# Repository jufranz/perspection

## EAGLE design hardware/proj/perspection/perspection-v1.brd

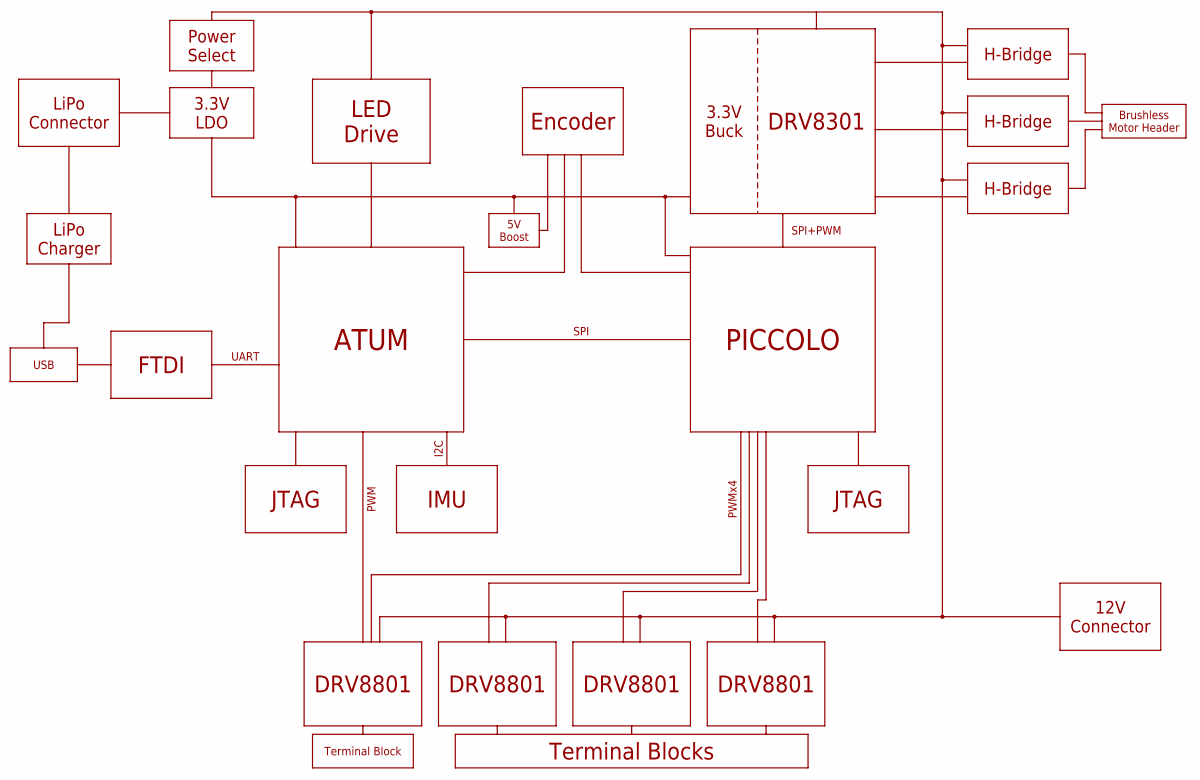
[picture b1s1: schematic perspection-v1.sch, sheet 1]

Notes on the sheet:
ATUM
PICCOLO
FTDI
SPI
UART
JTAG
DRV8301
H-Bridge
Brushless Motor Header
DRV8801
IMU
I2C
LED Drive
Terminal Blocks
Terminal Block
USB
Encoder
LiPo Charger
LiPo Connector
3.3V LDO
5V Boost
3.3V Buck
12V Connector
PWMx4
PWM
SPI+PWM
Power Select

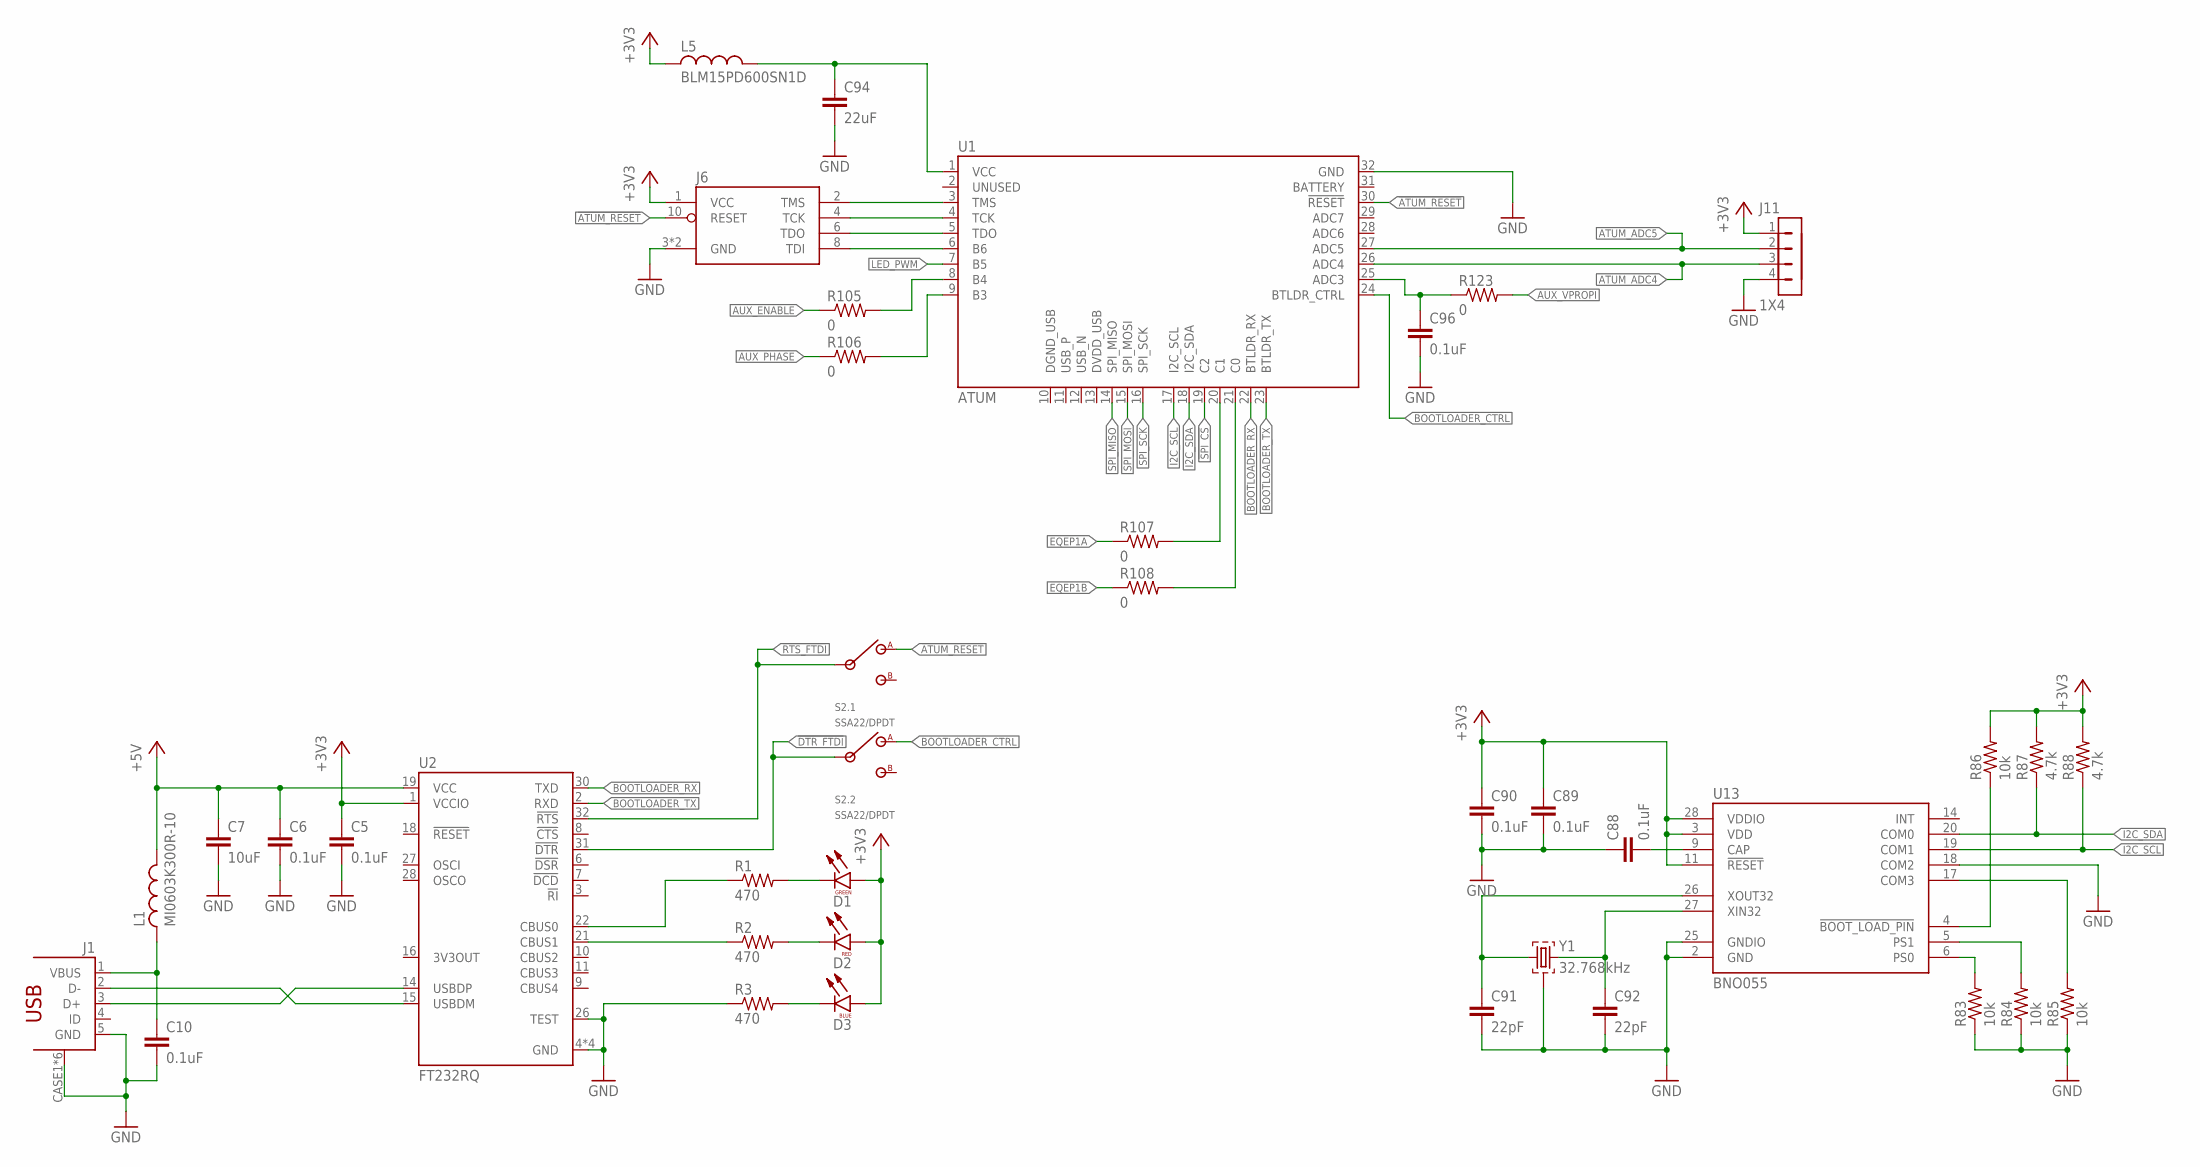
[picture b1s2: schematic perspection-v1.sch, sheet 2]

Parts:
C5, C6, C10, C88, C89, C90, C96: 0.1uF; C0402
C7: 10uF; C1206
C91, C92: 22pF; C0402
C94: 22uF; C1206
D1, D2, D3: LED0603
J1: MICRO-USB-10118192-0001LF; MICRO-USB
J6: JTAG-ARM_TC-10; TC2050-IDC
J11: 1X4; 1X4_0.1IN_THRUHOLE
L1: MI0603K300R-10; L0603; MFG_PN MI0603K300R-10
L5: BLM15PD600SN1D; L0402; MFG_PN BLM15PD600SN1D
R1, R2, R3: 470; R0402
R83, R84, R85, R86: 10k; R0402
R87, R88: 4.7k; R0402
R105, R106, R107, R108, R123: 0; R0402
S2: SSA22/DPDT
U1: ATUM
U2: FT232RQ; QFN32
U13: BNO055; LGA-28
Y1: 32.768kHz; SOJ-4

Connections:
!ATUM_RESET: J6.10 (RESET), S2.A1 (1), U1.30 (!RESET)
!DTR_FTDI: S2.COM2 (2), U2.31 (!DTR)
!RTS_FTDI: S2.COM1 (2), U2.32 (!RTS)
!SPI_CS: U1.19 (C2); also elsewhere on the board
+3V3: C5.1, C89.1, C90.1, D1.ANODE, D2.ANODE, D3.ANODE, J6.1 (VCC), J11.1, L5.1, R86.2, R87.2, R88.2, U2.1 (VCCIO), U13.3 (VDD), U13.11 (!RESET), U13.28 (VDDIO); also elsewhere on the board
+5V: C6.1, C7.1, L1.2, U2.19 (VCC); also elsewhere on the board
ATUM_ADC4: J11.3, U1.26 (ADC4)
ATUM_ADC5: J11.2, U1.27 (ADC5)
ATUM_C0: R108.2, U1.21 (C0)
ATUM_C1: R107.2, U1.20 (C1)
ATUM_TCK: J6.4 (TCK), U1.4 (TCK)
ATUM_TDO: J6.6 (TDO), U1.5 (TDO)
ATUM_TMS: J6.2 (TMS), U1.3 (TMS)
AUX_ENABLE: R105.1; also elsewhere on the board
AUX_PHASE: R106.1; also elsewhere on the board
AUX_VPROPI: R123.2; also elsewhere on the board
BOOTLOADER_CTRL: S2.A2 (1), U1.24 (BTLDR_CTRL)
BOOTLOADER_RX: U1.22 (BTLDR_RX), U2.30 (TXD)
BOOTLOADER_TX: U1.23 (BTLDR_TX), U2.2 (RXD)
D_N: J1.2 (D-), U2.15 (USBDM)
D_P: J1.3 (D+), U2.14 (USBDP)
EQEP1A: R107.1; also elsewhere on the board
EQEP1B: R108.1; also elsewhere on the board
GND: C5.2, C6.2, C7.2, C10.2, C88.1, C89.2, C90.2, C91.2, C92.2, C94.2, C96.2, J1.5 (GND), J1.CASE1 (MTN4), J1.CASE2 (MTN4), J1.CASE3 (MTN4), J1.CASE4 (MTN4), J1.CASE5 (MTN4), J1.CASE6 (MTN4), J6.3 (GND), J6.9 (GND), J11.4, R3.1, R83.1, R84.1, R85.1, U1.32 (GND), U2.4 (GND), U2.17 (GND), U2.20 (GND), U2.24 (GND), U2.26 (TEST), U13.2 (GND), U13.18 (COM2), U13.25 (GNDIO), Y1.2, Y1.3 (2); also elsewhere on the board
I2C_SCL: R88.1, U1.17 (I2C_SCL), U13.19 (COM1)
I2C_SDA: R87.1, U1.18 (I2C_SDA), U13.20 (COM0)
LED_PWM: U1.7 (B5); also elsewhere on the board
unnamed: D2.CATHODE, R2.2
unnamed: D1.CATHODE, R1.2
unnamed: R2.1, U2.21 (CBUS1)
unnamed: R1.1, U2.22 (CBUS0)
unnamed: D3.CATHODE, R3.2
unnamed: C96.1, R123.1, U1.25 (ADC3)
unnamed: C10.1, J1.1 (VBUS), L1.1
unnamed: R105.2, U1.8 (B4)
unnamed: R106.2, U1.9 (B3)
unnamed: R84.2, U13.5 (PS1)
unnamed: R83.2, U13.6 (PS0)
unnamed: C92.1, U13.27 (XIN32), Y1.4 (3)
unnamed: C88.2, U13.9 (CAP)
unnamed: C91.1, U13.26 (XOUT32), Y1.1
unnamed: R85.2, U13.17 (COM3)
unnamed: R86.1, U13.4 (!BOOT_LOAD_PIN)
unnamed: C94.1, L5.2, U1.1 (VCC)
unnamed: J6.8 (TDI), U1.6 (B6)
SPI_MISO: U1.14 (SPI_MISO); also elsewhere on the board
SPI_MOSI: U1.15 (SPI_MOSI); also elsewhere on the board
SPI_SCK: U1.16 (SPI_SCK); also elsewhere on the board

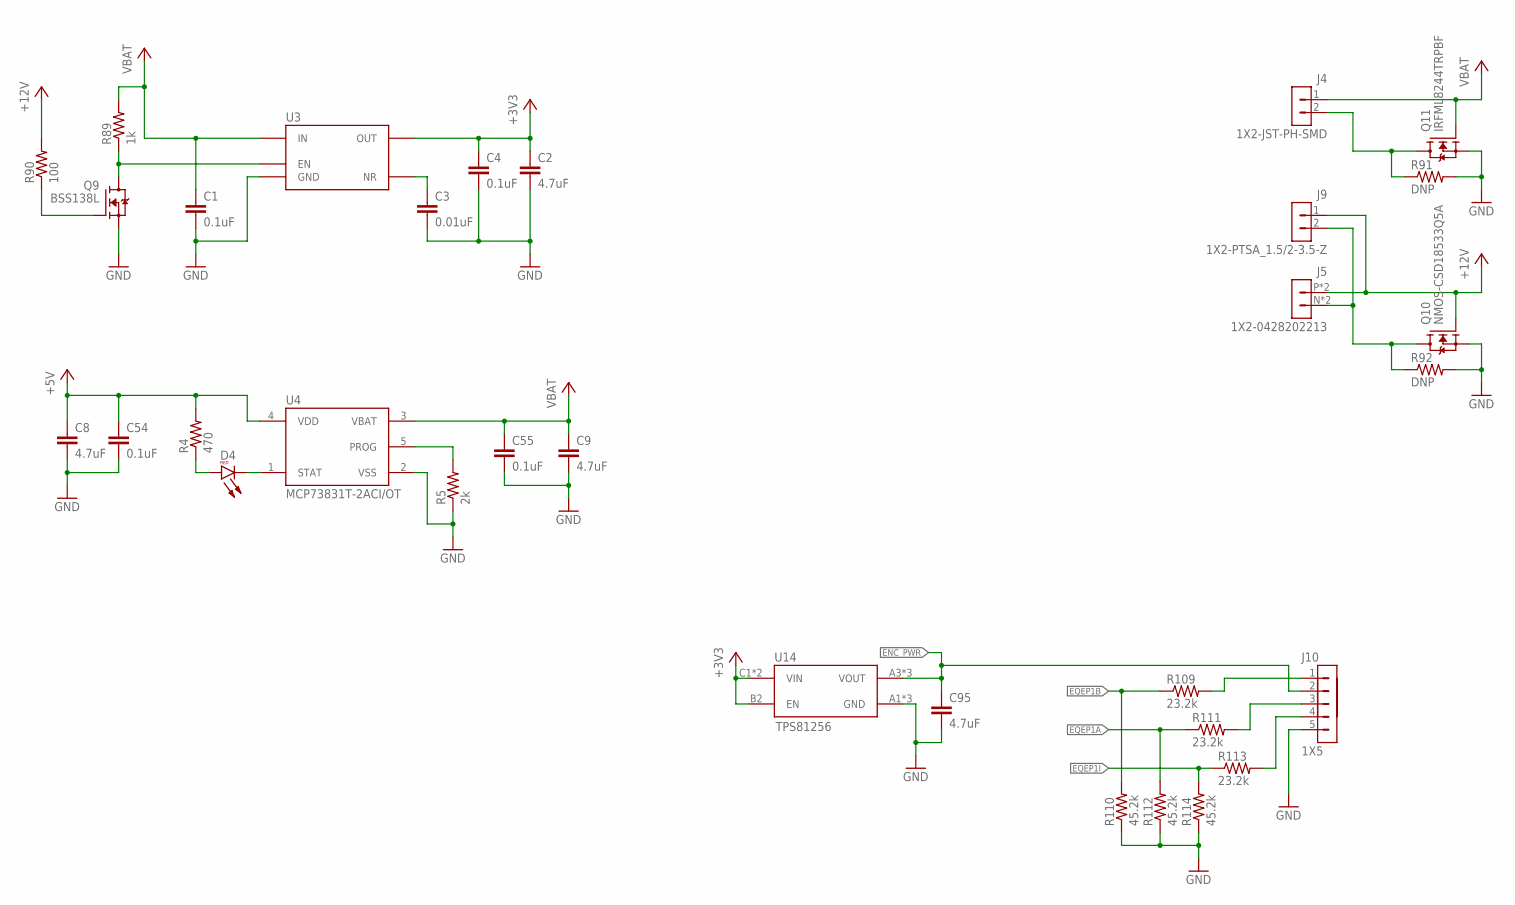
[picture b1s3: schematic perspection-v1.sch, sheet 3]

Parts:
C1, C4, C54, C55: 0.1uF; C0402
C2, C8, C9: 4.7uF; C0805
C3: 0.01uF; C0402
C95: 4.7uF; C0603
D4: LED0603
J4: 1X2-JST-PH-SMD; JST-PH-2-SMD
J5: 1X2-0428202213; MOLEX_SABRE_2POS
J9: 1X2-PTSA_1.5/2-3.5-Z; 3.5MM_PTSA_1.5/2-3.5-Z
J10: 1X5; 1X5_0.1IN_THRUHOLE
Q9: BSS138L; SOT23
Q10: NMOS-CSD18533Q5A; SON-5X6
Q11: IRFML8244TRPBF; SOT23
R4: 470; R0402
R5: 2k; R0402
R89: 1k; R0402
R90: 100; R0402
R91: DNP; R0402
R92: DNP; R0805
R109, R111, R113: 23.2k; R0402
R110, R112, R114: 45.2k; R0402
U3: TPS79933DDCR; SOT23-5
U4: MCP73831T-2ACI/OT; SOT23-5
U14: TPS81256; TI-SIP-9

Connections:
+3V3: C2.1, C4.1, U3.5 (OUT), U14.B2 (EN), U14.C1 (VIN), U14.C2 (VIN); also elsewhere on the board
+5V: C8.1, C54.1, R4.2, U4.4 (VDD); also elsewhere on the board
+12V: J5.P (1), J5.P2 (1), J9.1, Q10.G, R90.2; also elsewhere on the board
+12V_GND: J5.N (2), J5.N2 (2), J9.2, Q10.D, R92.1
ENC_PWR: C95.1, J10.2, U14.A3 (VOUT), U14.B3 (VOUT), U14.C3 (VOUT)
EQEP1A: R111.1, R112.2; also elsewhere on the board
EQEP1B: R109.1, R110.2; also elsewhere on the board
EQEP1I: R113.1, R114.2; also elsewhere on the board
GND: C1.2, C2.2, C3.2, C4.2, C8.2, C9.2, C54.2, C55.2, C95.2, J10.5, Q9.2 (S), Q10.S1 (S), Q10.S2 (S), Q10.S3 (S), Q11.2 (S), R5.1, R91.2, R92.2, R110.1, R112.1, R114.1, U3.2 (GND), U4.2 (VSS), U14.A1 (GND), U14.A2 (GND), U14.B1 (GND); also elsewhere on the board
unnamed: J10.1, R109.2
unnamed: D4.CATHODE, U4.1 (STAT)
unnamed: C3.1, U3.4 (NR)
unnamed: D4.ANODE, R4.1
unnamed: R5.2, U4.5 (PROG)
unnamed: J10.3, R111.2
unnamed: J10.4, R113.2
unnamed: Q9.3 (D), R89.1, U3.3 (EN)
unnamed: Q9.1 (G), R90.1
VBAT: C1.1, C9.1, C55.1, J4.1, Q11.1 (G), R89.2, U3.1 (IN), U4.3 (VBAT)
VBAT_GND: J4.2, Q11.3 (D), R91.1

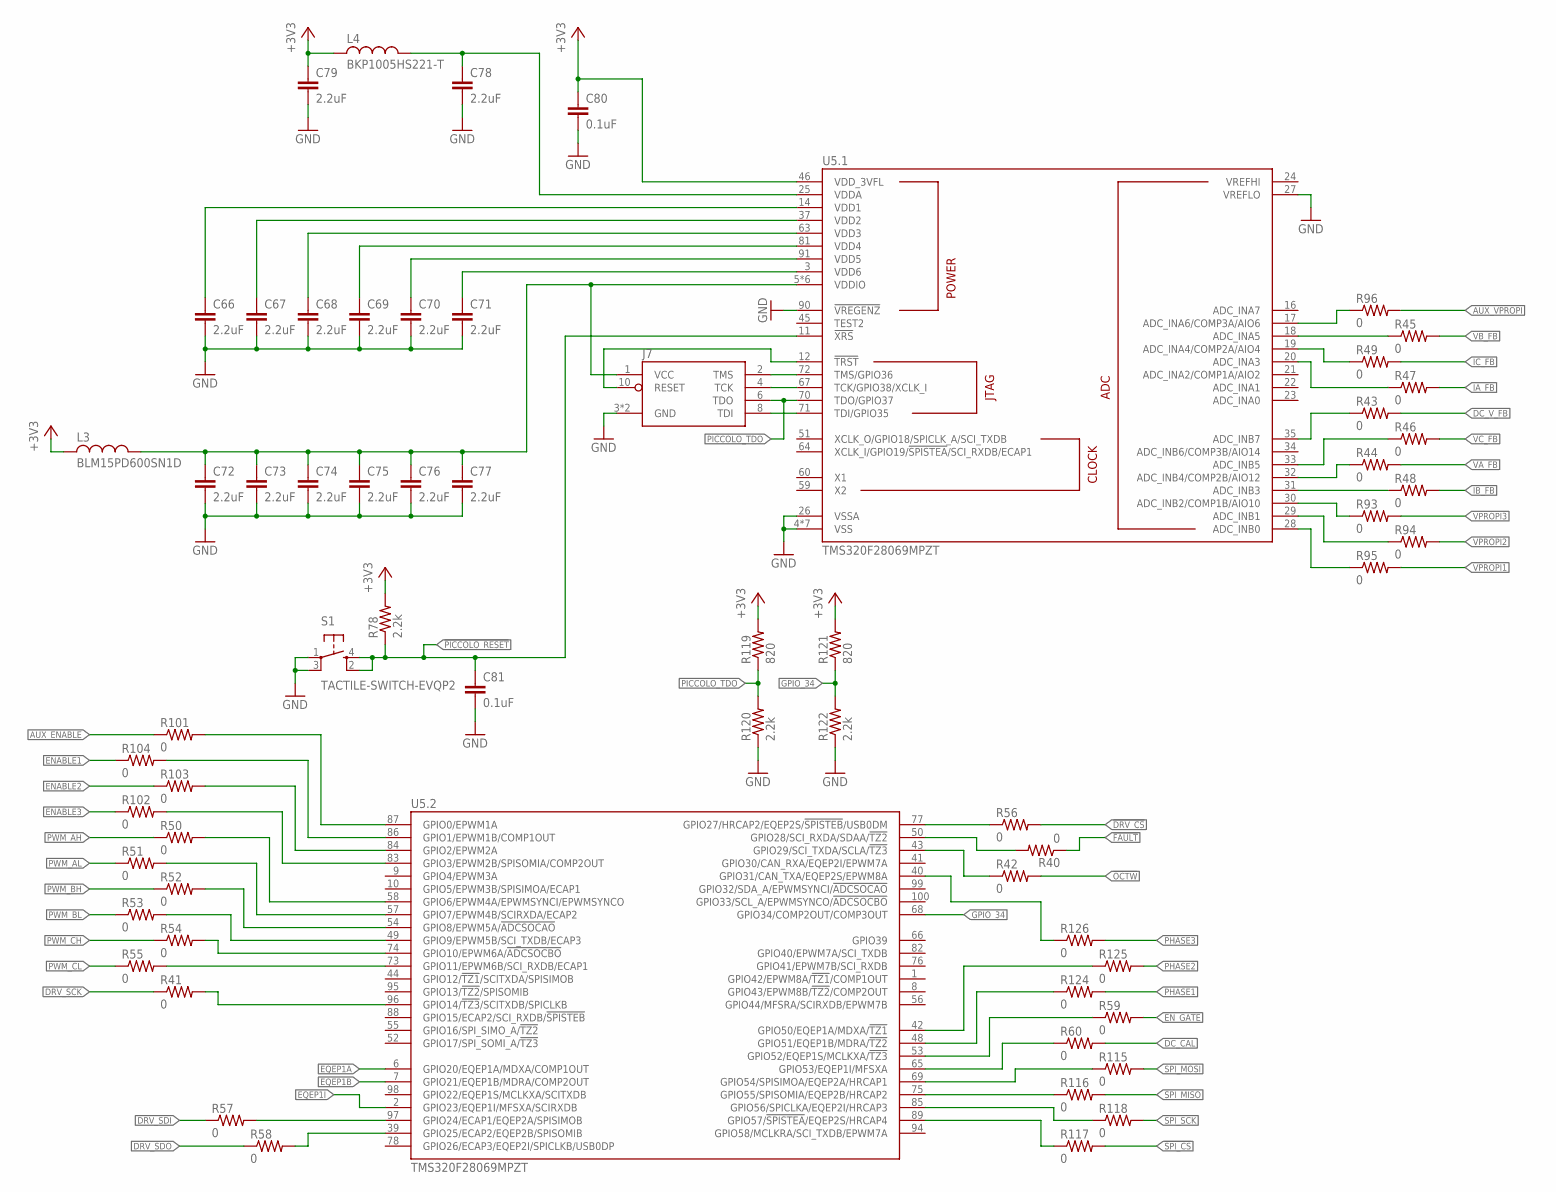
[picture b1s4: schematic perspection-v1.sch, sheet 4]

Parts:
C66, C67, C68, C69, C70, C71, C72, C73, C74, C75, C76, C77, C78, C79: 2.2uF; C0402
C80, C81: 0.1uF; C0402
J7: JTAG-ARM_TC-10; TC2050-IDC
L3: BLM15PD600SN1D; L0402; MFG_PN BLM15PD600SN1D
L4: BKP1005HS221-T; L0402
R40, R41, R42, R43, R44, R45, R46, R47, R48, R49, R50, R51, R52, R53, R54, R55, R56, R57, R58, R59, R60, R93, R94, R95, R96, R101, R102, R103, R104, R115, R116, R117, R118, R124, R125, R126: 0; R0402
R78, R120, R122: 2.2k; R0402
R119, R121: 820; R0402
S1: TACTILE-SWITCH-EVQP2; EVQP2
U5: TMS320F28069MPZT; TI-LQFP-100

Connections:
!DRV_CS: R56.2; also elsewhere on the board
!FAULT: R40.1; also elsewhere on the board
!OCTW: R42.2; also elsewhere on the board
!PICCOLO_RESET: C81.1, R78.1, S1.2 (4), S1.4 (3), U5.11 (!XRS)
!PICCOLO_TRST: J7.10 (RESET), U5.12 (!TRST)
!SPI_CS: R117.2; also elsewhere on the board
+3V3: C79.1, C80.1, L3.1, L4.1, R78.2, R119.2, R121.2, U5.46 (VDD_3VFL); also elsewhere on the board
AUX_ENABLE: R101.1; also elsewhere on the board
AUX_VPROPI: R96.2; also elsewhere on the board
DC_CAL: R60.2; also elsewhere on the board
DC_V_FB: R43.2; also elsewhere on the board
DRV_SCK: R41.1; also elsewhere on the board
DRV_SDI: R57.1; also elsewhere on the board
DRV_SDO: R58.1; also elsewhere on the board
ENABLE1: R104.1; also elsewhere on the board
ENABLE2: R103.1; also elsewhere on the board
ENABLE3: R102.1; also elsewhere on the board
EN_GATE: R59.2; also elsewhere on the board
EQEP1A: U5.6 (GPIO20/EQEP1A/MDXA/COMP1OUT); also elsewhere on the board
EQEP1B: U5.7 (GPIO21/EQEP1B/MDRA/COMP2OUT); also elsewhere on the board
EQEP1I: U5.2 (GPIO23/EQEP1I/MFSXA/SCIRXDB); also elsewhere on the board
GND: C66.2, C67.2, C68.2, C69.2, C70.2, C71.2, C72.2, C73.2, C74.2, C75.2, C76.2, C77.2, C78.2, C79.2, C80.2, C81.2, J7.3 (GND), J7.9 (GND), R120.1, R122.1, S1.1, S1.3 (2), U5.4 (VSS), U5.15 (VSS), U5.26 (VSSA), U5.27 (VREFLO), U5.36 (VSS), U5.47 (VSS), U5.62 (VSS), U5.80 (VSS), U5.90 (!VREGENZ), U5.92 (VSS); also elsewhere on the board
GPIO_34: R121.1, R122.2, U5.68 (GPIO34/COMP2OUT/COMP3OUT)
IA_FB: R47.2; also elsewhere on the board
IB_FB: R48.2; also elsewhere on the board
IC_FB: R49.2; also elsewhere on the board
unnamed: R57.2, U5.97 (GPIO24/ECAP1/EQEP2A/SPISIMOB)
unnamed: R93.1, U5.30 (ADC_INB2/COMP1B/AIO10)
unnamed: R94.1, U5.29 (ADC_INB1)
unnamed: R95.1, U5.28 (ADC_INB0)
unnamed: R96.1, U5.17 (ADC_INA6/COMP3A/AIO6)
unnamed: R102.2, U5.83 (GPIO3/EPWM2B/SPISOMIA/COMP2OUT)
unnamed: R103.2, U5.84 (GPIO2/EPWM2A)
unnamed: R104.2, U5.86 (GPIO1/EPWM1B/COMP1OUT)
unnamed: R101.2, U5.87 (GPIO0/EPWM1A)
unnamed: R42.1, U5.43 (GPIO29/SCI_TXDA/SCLA/!TZ3)
unnamed: R126.1, U5.40 (GPIO31/CAN_TXA/EQEP2S/EPWM8A)
unnamed: C72.1, C73.1, C74.1, C75.1, C76.1, C77.1, J7.1 (VCC), L3.2, U5.5 (VDDIO), U5.13 (VDDIO), U5.38 (VDDIO), U5.61 (VDDIO), U5.79 (VDDIO), U5.93 (VDDIO)
unnamed: R40.2, U5.50 (GPIO28/SCI_RXDA/SDAA/!TZ2)
unnamed: C78.1, L4.2, U5.25 (VDDA)
PHASE1: R124.2; also elsewhere on the board
PHASE2: R125.2; also elsewhere on the board
PHASE3: R126.2; also elsewhere on the board
PICCOLO_TCK: J7.4 (TCK), U5.67 (TCK/GPIO38/XCLK_I)
PICCOLO_TDI: J7.8 (TDI), U5.71 (TDI/GPIO35)
PICCOLO_TDO: J7.6 (TDO), R119.1, R120.2, U5.70 (TDO/GPIO37)
PICCOLO_TMS: J7.2 (TMS), U5.72 (TMS/GPIO36)
PWM_AH: R50.1; also elsewhere on the board
PWM_AL: R51.1; also elsewhere on the board
PWM_BH: R52.1; also elsewhere on the board
PWM_BL: R53.1; also elsewhere on the board
PWM_CH: R54.1; also elsewhere on the board
PWM_CL: R55.1; also elsewhere on the board
SPI_MISO: R116.2; also elsewhere on the board
SPI_MOSI: R115.2; also elsewhere on the board
SPI_SCK: R118.2; also elsewhere on the board
VA_FB: R44.2; also elsewhere on the board
VB_FB: R45.2; also elsewhere on the board
VC_FB: R46.2; also elsewhere on the board
VDD1: C66.1, U5.14 (VDD1)
VDD2: C67.1, U5.37 (VDD2)
VDD3: C68.1, U5.63 (VDD3)
VDD4: C69.1, U5.81 (VDD4)
VDD5: C70.1, U5.91 (VDD5)
VDD6: C71.1, U5.3 (VDD6)
VPROPI1: R95.2; also elsewhere on the board
VPROPI2: R94.2; also elsewhere on the board
VPROPI3: R93.2; also elsewhere on the board
_!DRV_CS: R56.1, U5.77 (GPIO27/HRCAP2/EQEP2S/!SPISTEB!/USB0DM)
_!SPI_CS: R117.1, U5.89 (GPIO57/!SPISTEA!/EQEP2S/HRCAP4)
_DC_CAL: R60.1, U5.65 (GPIO53/EQEP1I/MFSXA)
_DC_V_FB: R43.1, U5.35 (ADC_INB7)
_DRV_SCK: R41.2, U5.96 (GPIO14/!TZ3!/SCITXDB/SPICLKB)
_DRV_SDO: R58.2, U5.39 (GPIO25/ECAP2/EQEP2B/SPISOMIB)
_EN_GATE: R59.1, U5.53 (GPIO52/EQEP1S/MCLKXA/!TZ3)
_PHASE1: R124.1, U5.48 (GPIO51/EQEP1B/MDRA/!TZ2)
_PHASE2: R125.1, U5.42 (GPIO50/EQEP1A/MDXA/!TZ1)
_PWM_AH: R50.2, U5.58 (GPIO6/EPWM4A/EPWMSYNCI/EPWMSYNCO)
_PWM_AL: R51.2, U5.57 (GPIO7/EPWM4B/SCIRXDA/ECAP2)
_PWM_BH: R52.2, U5.54 (GPIO8/EPWM5A/!ADCSOCAO)
_PWM_BL: R53.2, U5.49 (GPIO9/EPWM5B/SCI_TXDB/ECAP3)
_PWM_CH: R54.2, U5.74 (GPIO10/EPWM6A/!ADCSOCBO)
_PWM_CL: R55.2, U5.73 (GPIO11/EPWM6B/SCI_RXDB/ECAP1)
_SPI_MISO: R116.1, U5.75 (GPIO55/SPISOMIA/EQEP2B/HRCAP2)
_SPI_MOSI: R115.1, U5.69 (GPIO54/SPISIMOA/EQEP2A/HRCAP1)
_SPI_SCK: R118.1, U5.85 (GPIO56/SPICLKA/EQEP2I/HRCAP3)
_VA_FB: R44.1, U5.32 (ADC_INB4/COMP2B/AIO12)
_VB_FB: R45.1, U5.18 (ADC_INA5)
_VC_FB: R46.1, U5.33 (ADC_INB5)
__IA_FB: R47.1, U5.20 (ADC_INA3)
__IB_FB: R48.1, U5.31 (ADC_INB3)
__IC_FB: R49.1, U5.19 (ADC_INA4/COMP2A/AIO4)

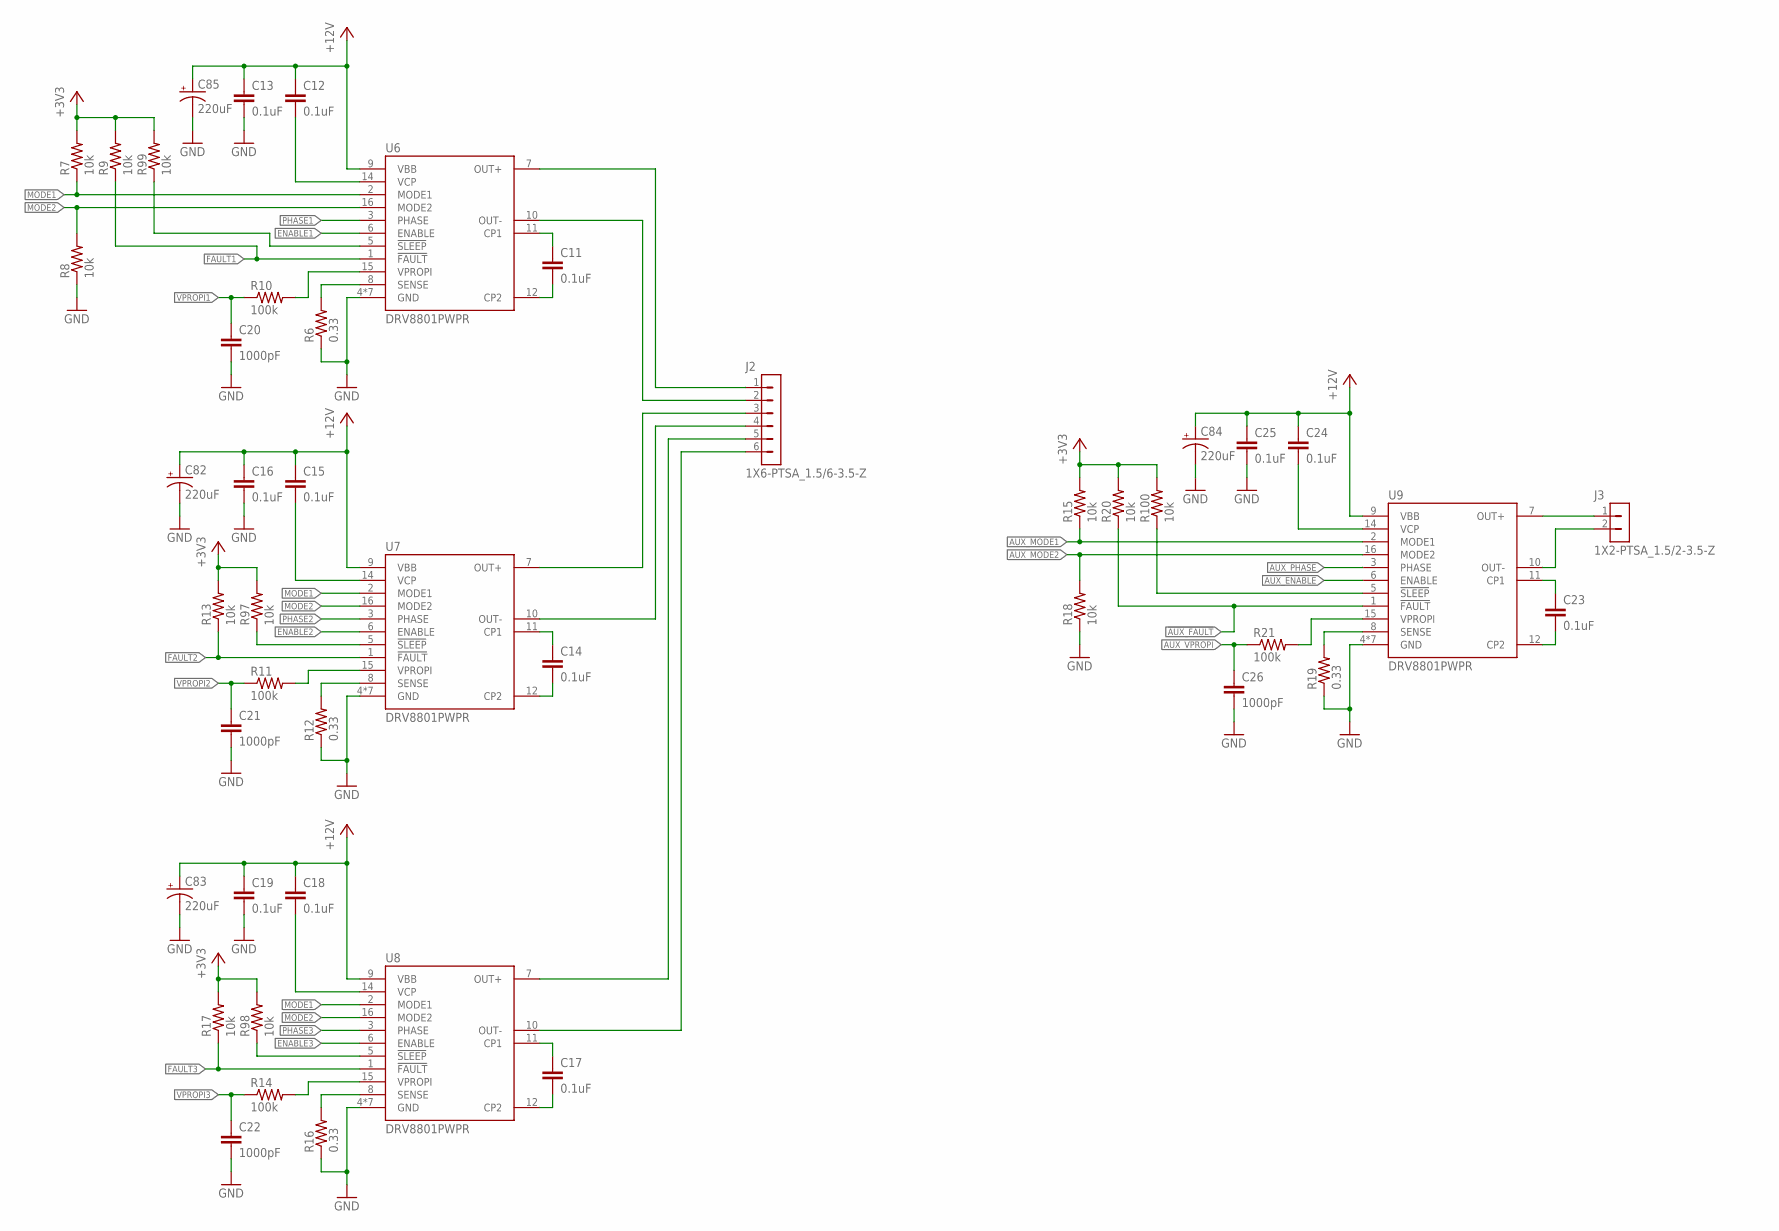
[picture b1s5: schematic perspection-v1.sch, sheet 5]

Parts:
C11, C12, C13, C14, C15, C16, C17, C18, C19, C23, C24, C25: 0.1uF; C0402
C20, C21, C22, C26: 1000pF; C0402
C82, C83, C84, C85: 220uF; PANASONIC-6.3MM-SMD
J2: 1X6-PTSA_1.5/6-3.5-Z; 3.5MM_PTSA_1.5/6-3.5-Z
J3: 1X2-PTSA_1.5/2-3.5-Z; 3.5MM_PTSA_1.5/2-3.5-Z
R6, R12, R16, R19: 0.33; R1206; MFG_PN RUT3216FR330CS
R7, R8, R9, R13, R15, R17, R18, R20, R97, R98, R99, R100: 10k; R0402
R10, R11, R14, R21: 100k; R0402
U6, U7, U8, U9: DRV8801PWPR; TI-HTSSOP-16

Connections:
!AUX_FAULT: R20.1, U9.1 (!FAULT)
!AUX_SLEEP: R100.1, U9.5 (!SLEEP)
!SLEEP1: R99.1, U6.5 (!SLEEP)
!SLEEP2: R97.1, U7.5 (!SLEEP)
!SLEEP3: R98.1, U8.5 (!SLEEP)
+3V3: R7.2, R9.2, R13.2, R15.2, R17.2, R20.2, R97.2, R98.2, R99.2, R100.2; also elsewhere on the board
+12V: C12.1, C13.1, C15.1, C16.1, C18.1, C19.1, C24.1, C25.1, C82.POS (+), C83.POS (+), C84.POS (+), C85.POS (+), U6.9 (VBB), U7.9 (VBB), U8.9 (VBB), U9.9 (VBB); also elsewhere on the board
AUX_ENABLE: U9.6 (ENABLE); also elsewhere on the board
AUX_MODE1: R15.1, U9.2 (MODE1)
AUX_MODE2: R18.2, U9.16 (MODE2)
AUX_PHASE: U9.3 (PHASE); also elsewhere on the board
AUX_SENSE: R19.2, U9.8 (SENSE)
AUX_VPROPI: C26.1, R21.1; also elsewhere on the board
ENABLE1: U6.6 (ENABLE); also elsewhere on the board
ENABLE2: U7.6 (ENABLE); also elsewhere on the board
ENABLE3: U8.6 (ENABLE); also elsewhere on the board
FAULT1: R9.1, U6.1 (!FAULT)
FAULT2: R13.1, U7.1 (!FAULT)
FAULT3: R17.1, U8.1 (!FAULT)
GND: C13.2, C16.2, C19.2, C20.2, C21.2, C22.2, C25.2, C26.2, C82.NEG (-), C83.NEG (-), C84.NEG (-), C85.NEG (-), R6.1, R8.1, R12.1, R16.1, R18.1, R19.1, U6.4 (GND), U6.13 (GND), U6.PAD (GND), U6.THERM1 (GND), U6.THERM2 (GND), U6.THERM3 (GND), U6.THERM4 (GND), U7.4 (GND), U7.13 (GND), U7.PAD (GND), U7.THERM1 (GND), U7.THERM2 (GND), U7.THERM3 (GND), U7.THERM4 (GND), U8.4 (GND), U8.13 (GND), U8.PAD (GND), U8.THERM1 (GND), U8.THERM2 (GND), U8.THERM3 (GND), U8.THERM4 (GND), U9.4 (GND), U9.13 (GND), U9.PAD (GND), U9.THERM1 (GND), U9.THERM2 (GND), U9.THERM3 (GND), U9.THERM4 (GND); also elsewhere on the board
M1+: J2.1, U6.7 (OUT+)
M1-: J2.2, U6.10 (OUT-)
M2+: J2.3, U7.7 (OUT+)
M2-: J2.4, U7.10 (OUT-)
M3+: J2.5, U8.7 (OUT+)
M3-: J2.6, U8.10 (OUT-)
MODE1: R7.1, U6.2 (MODE1), U7.2 (MODE1), U8.2 (MODE1)
MODE2: R8.2, U6.16 (MODE2), U7.16 (MODE2), U8.16 (MODE2)
M_AUX+: J3.1, U9.7 (OUT+)
M_AUX-: J3.2, U9.10 (OUT-)
unnamed: C11.2, U6.12 (CP2)
unnamed: C11.1, U6.11 (CP1)
unnamed: C12.2, U6.14 (VCP)
unnamed: C14.2, U7.12 (CP2)
unnamed: C14.1, U7.11 (CP1)
unnamed: C15.2, U7.14 (VCP)
unnamed: C17.2, U8.12 (CP2)
unnamed: C17.1, U8.11 (CP1)
unnamed: C18.2, U8.14 (VCP)
unnamed: C23.2, U9.12 (CP2)
unnamed: C23.1, U9.11 (CP1)
unnamed: C24.2, U9.14 (VCP)
PHASE1: U6.3 (PHASE); also elsewhere on the board
PHASE2: U7.3 (PHASE); also elsewhere on the board
PHASE3: U8.3 (PHASE); also elsewhere on the board
SENSE1: R6.2, U6.8 (SENSE)
SENSE2: R12.2, U7.8 (SENSE)
SENSE3: R16.2, U8.8 (SENSE)
VPROPI1: C20.1, R10.1; also elsewhere on the board
VPROPI2: C21.1, R11.1; also elsewhere on the board
VPROPI3: C22.1, R14.1; also elsewhere on the board
_AUX_VPROPI: R21.2, U9.15 (VPROPI)
_VPROPI1: R10.2, U6.15 (VPROPI)
_VPROPI2: R11.2, U7.15 (VPROPI)
_VPROPI3: R14.2, U8.15 (VPROPI)

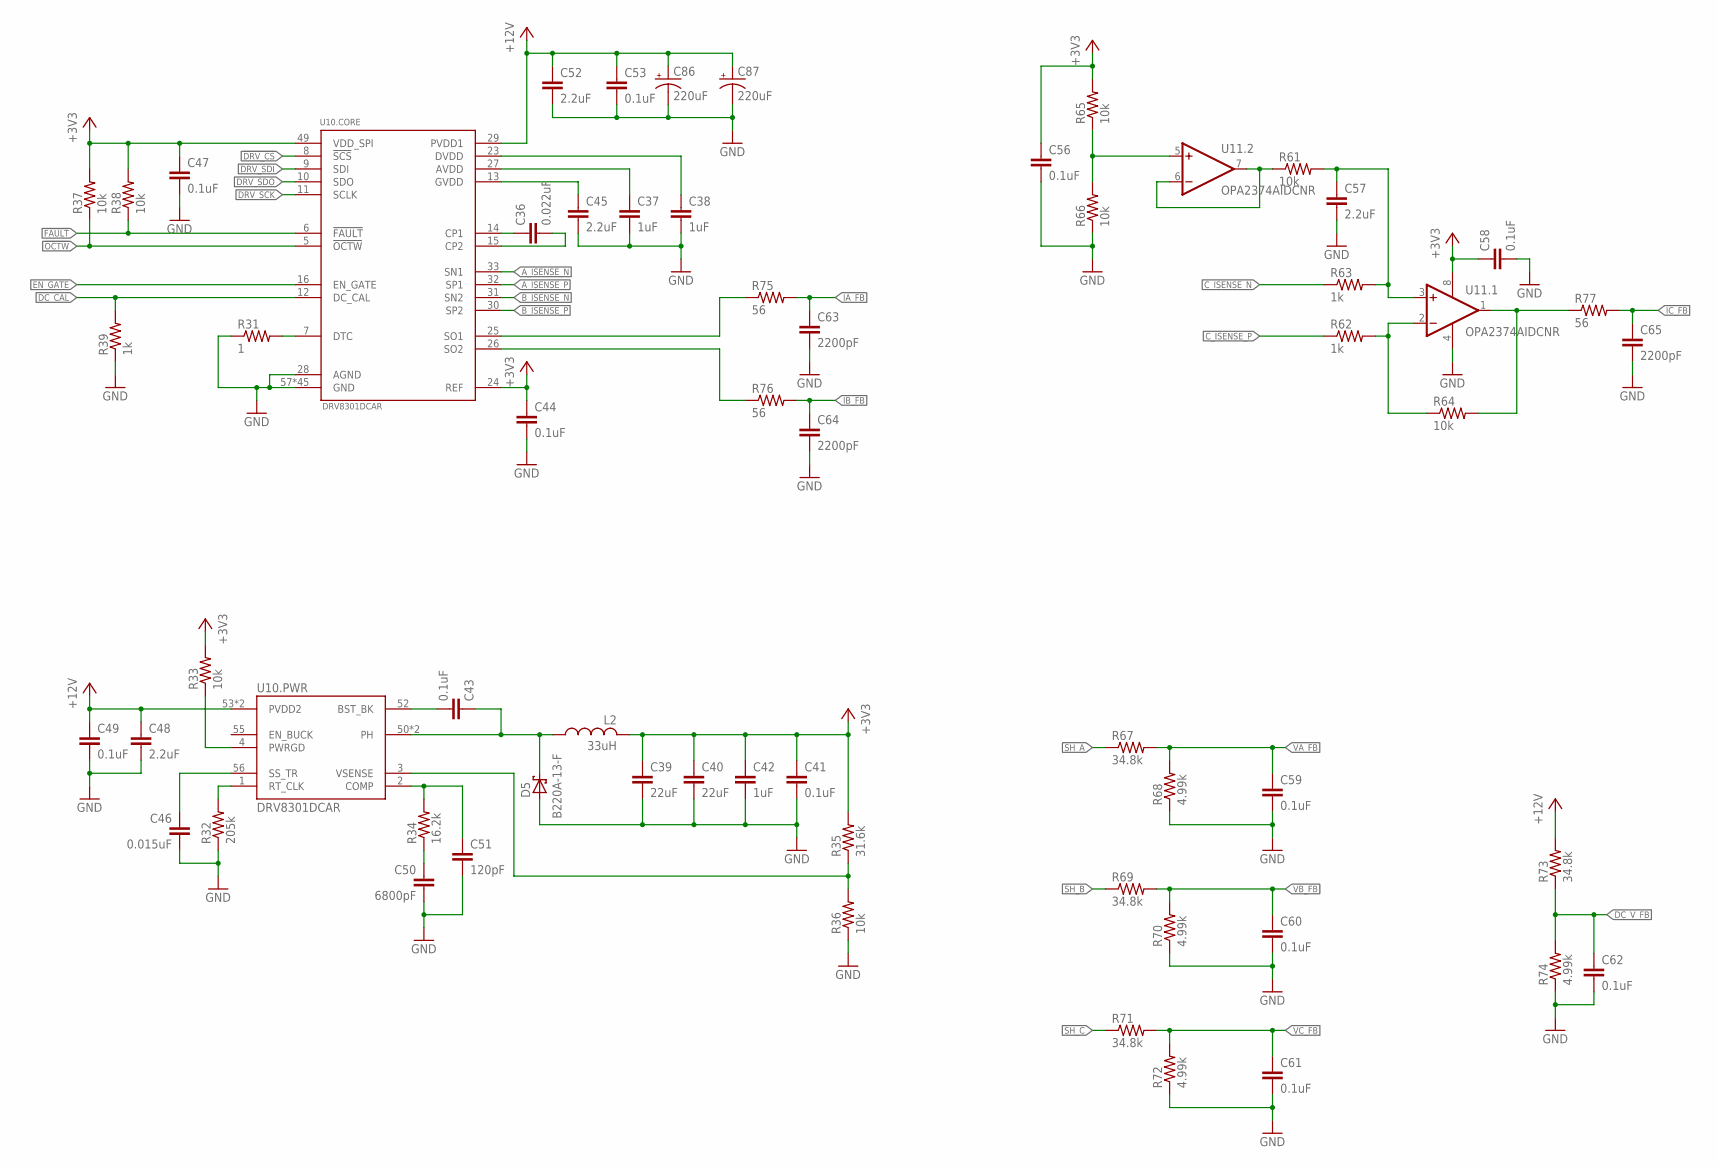
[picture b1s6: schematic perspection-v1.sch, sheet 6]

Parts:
C36: 0.022uF; C0402
C37, C38: 1uF; C0402
C39, C40: 22uF; C1210
C41, C43, C44, C47, C49, C53, C56, C58, C59, C60, C61, C62: 0.1uF; C0402
C42: 1uF; C0805
C45: 2.2uF; C0603
C46: 0.015uF; C0402
C48, C52: 2.2uF; C0805
C50: 6800pF; C0402
C51: 120pF; C0402
C57: 2.2uF; C0402
C63, C64, C65: 2200pF; C0402
C86, C87: 220uF; PANASONIC-6.3MM-SMD
D5: B220A-13-F; SMB
L2: 33uH; DR74
R31: 1; R0402
R32: 205k; R0402
R33, R36, R37, R38, R61, R64, R65, R66: 10k; R0402
R34: 16.2k; R0402
R35: 31.6k; R0402
R39, R62, R63: 1k; R0402
R67, R69, R71, R73: 34.8k; R0402
R68, R70, R72, R74: 4.99k; R0402
R75, R76, R77: 56; R0402
U10: DRV8301DCAR; TI-HTSSOP-56
U11: OPA2374AIDCNR; TI-SOT23-8

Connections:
!DRV_CS: U10.8 (!SCS); also elsewhere on the board
!FAULT: R38.1, U10.6 (!FAULT); also elsewhere on the board
!OCTW: R37.1, U10.5 (!OCTW); also elsewhere on the board
+3V3: C39.1, C40.1, C41.1, C42.1, C44.1, C47.1, C56.1, C58.1, L2.1, R33.2, R35.2, R37.2, R38.2, R65.2, U10.24 (REF), U10.49 (VDD_SPI), U11.8 (V+); also elsewhere on the board
+12V: C48.1, C49.1, C52.1, C53.1, C86.POS (+), C87.POS (+), R73.2, U10.29 (PVDD1), U10.53 (PVDD2), U10.54 (PVDD2); also elsewhere on the board
AVDD: C37.1, U10.27 (AVDD)
A_ISENSE_N: U10.33 (SN1); also elsewhere on the board
A_ISENSE_P: U10.32 (SP1); also elsewhere on the board
BST_BK: C43.2, U10.52 (BST_BK)
B_ISENSE_N: U10.31 (SN2); also elsewhere on the board
B_ISENSE_P: U10.30 (SP2); also elsewhere on the board
COMP: C51.1, R34.2, U10.2 (COMP)
C_ISENSE_N: R63.1; also elsewhere on the board
C_ISENSE_P: R62.1; also elsewhere on the board
DC_CAL: R39.2, U10.12 (DC_CAL); also elsewhere on the board
DC_V_FB: C62.1, R73.1, R74.2; also elsewhere on the board
DRV_SCK: U10.11 (SCLK); also elsewhere on the board
DRV_SDI: U10.9 (SDI); also elsewhere on the board
DRV_SDO: U10.10 (SDO); also elsewhere on the board
DTC: R31.2, U10.7 (DTC)
DVDD: C38.1, U10.23 (DVDD)
EN_GATE: U10.16 (EN_GATE); also elsewhere on the board
GND: C37.2, C38.2, C39.2, C40.2, C41.2, C42.2, C44.2, C45.2, C46.2, C47.2, C48.2, C49.2, C50.2, C51.2, C52.2, C53.2, C56.2, C57.2, C58.2, C59.2, C60.2, C61.2, C62.2, C63.2, C64.2, C65.2, C86.NEG (-), C87.NEG (-), D5.A, R31.1, R32.1, R36.1, R39.1, R66.1, R68.1, R70.1, R72.1, R74.1, U10.28 (AGND), U10.57 (GND), U10.P$58 (GND), U10.P$59 (GND), U10.P$60 (GND), U10.P$61 (GND), U10.P$62 (GND), U10.P$63 (GND), U10.P$64 (GND), U10.P$65 (GND), U10.P$66 (GND), U10.P$67 (GND), U10.P$68 (GND), U10.P$69 (GND), U10.P$70 (GND), U10.P$71 (GND), U10.P$72 (GND), U10.P$73 (GND), U10.P$74 (GND), U10.P$75 (GND), U10.P$76 (GND), U10.P$77 (GND), U10.P$78 (GND), U10.P$79 (GND), U10.P$80 (GND), U10.P$81 (GND), U10.P$82 (GND), U10.P$83 (GND), U10.P$84 (GND), U10.P$85 (GND), U10.P$86 (GND), U10.P$87 (GND), U10.P$88 (GND), U10.P$89 (GND), U10.P$90 (GND), U10.P$91 (GND), U10.P$92 (GND), U10.P$93 (GND), U10.P$94 (GND), U10.P$95 (GND), U10.P$96 (GND), U10.P$97 (GND), U10.P$98 (GND), U10.P$99 (GND), U10.P$100 (GND), U10.P$101 (GND), U11.4 (V-); also elsewhere on the board
GVDD: C45.1, U10.13 (GVDD)
IA_FB: C63.1, R75.2; also elsewhere on the board
IB_FB: C64.1, R76.2; also elsewhere on the board
IC_FB: C65.1, R77.2; also elsewhere on the board
unnamed: C36.1, U10.14 (CP1)
unnamed: C36.2, U10.15 (CP2)
unnamed: R61.1, U11.6 (-IN), U11.7 (OUT)
unnamed: C57.1, R61.2, R63.2, U11.3 (+IN)
unnamed: R62.2, R64.1, U11.2 (-IN)
unnamed: R65.1, R66.2, U11.5 (+IN)
PH: C43.1, D5.C, L2.2, U10.50 (PH), U10.51 (PH)
PWRGD: R33.1, U10.4 (PWRGD)
RT_CLK: R32.2, U10.1 (RT_CLK)
SH_A: R67.1; also elsewhere on the board
SH_B: R69.1; also elsewhere on the board
SH_C: R71.1; also elsewhere on the board
SS_TR: C46.1, U10.56 (SS_TR)
VA_FB: C59.1, R67.2, R68.2; also elsewhere on the board
VB_FB: C60.1, R69.2, R70.2; also elsewhere on the board
VC_FB: C61.1, R71.2, R72.2; also elsewhere on the board
VFB: R35.1, R36.2, U10.3 (VSENSE)
_COMP: C50.1, R34.1
_IA_FB: R75.1, U10.25 (SO1)
_IB_FB: R76.1, U10.26 (SO2)
_IC_FB: R64.2, R77.1, U11.1 (OUT)

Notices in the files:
software/c2000/PWMtest.c:
$Copyright: Copyright (C) 2008-2015 Texas Instruments Incorporated -
http://www.ti.com/ ALL RIGHTS RESERVED $
